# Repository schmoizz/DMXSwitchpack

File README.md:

# DMXSwitchpack
This project includes the PCB and Firmware to build a DIY DMX Switchpack

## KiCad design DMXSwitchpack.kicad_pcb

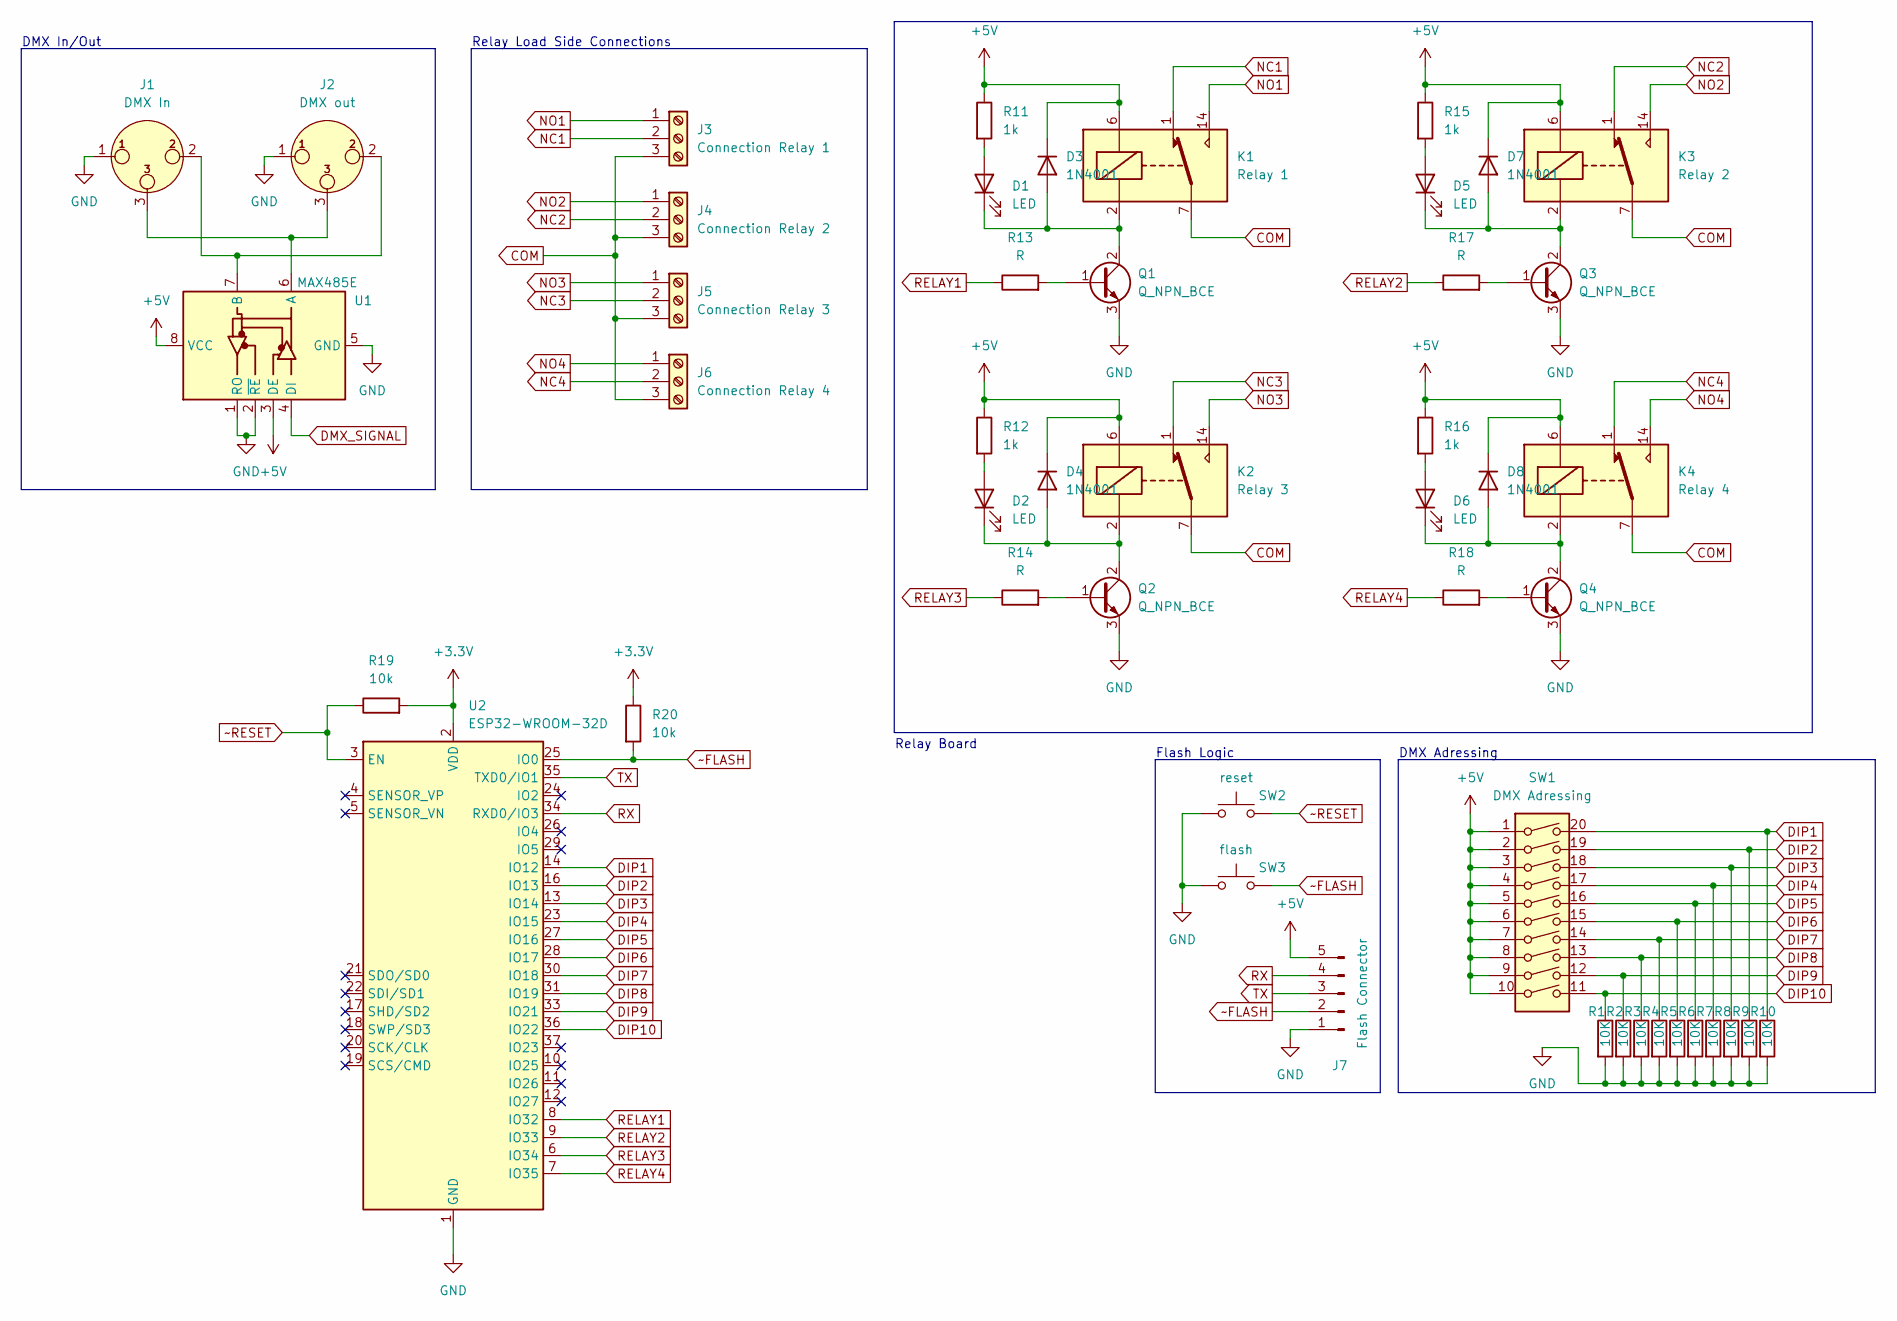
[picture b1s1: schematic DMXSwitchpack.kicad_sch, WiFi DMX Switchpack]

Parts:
D1, D2, D5, D6: LED; LED_0805_2012Metric_Pad1.15x1.40mm_HandSolder
D3, D4, D7, D8: 1N4001; D_DO-41_SOD81_P10.16mm_Horizontal
J1: DMX In; Jack_XLR_Neutrik_NC3FAAH-0_Horizontal
J2: DMX out; Jack_XLR_Neutrik_NC3FAAH-0_Horizontal
J3: Connection Relay 1; TerminalBlock_bornier-3_P5.08mm
J4: Connection Relay 2; TerminalBlock_bornier-3_P5.08mm
J5: Connection Relay 3; TerminalBlock_bornier-3_P5.08mm
J6: Connection Relay 4; TerminalBlock_bornier-3_P5.08mm
J7: Flash Connector; PinHeader_1x05_P2.54mm_Vertical
K1: Relay 1; Relay_StandexMeder_DIP_LowProfile
K2: Relay 3; Relay_StandexMeder_DIP_LowProfile
K3: Relay 2; Relay_StandexMeder_DIP_LowProfile
K4: Relay 4; Relay_StandexMeder_DIP_LowProfile
Q1, Q2, Q3, Q4: Q_NPN_BCE; LaserDiode_TO3.3-D3.3-3
R1, R2, R3, R4, R5, R6, R7, R8, R9, R10: 10K; R_0805_2012Metric_Pad1.20x1.40mm_HandSolder
R11, R12, R15, R16: 1k; R_0805_2012Metric_Pad1.20x1.40mm_HandSolder
R13, R14, R17, R18: R; R_0805_2012Metric_Pad1.20x1.40mm_HandSolder
R19, R20: 10k; R_0805_2012Metric_Pad1.20x1.40mm_HandSolder
SW1: DMX Adressing; SW_DIP_SPSTx10_Slide_9.78x27.58mm_W7.62mm_P2.54mm
SW2: reset; SW_PUSH_6mm_H5mm
SW3: flash; SW_PUSH_6mm_H5mm
U1: MAX485E; Broadcom_LGA-8_2x2mm_P0.53mm
U2: ESP32-WROOM-32D; ESP32-WROOM-32

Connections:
+3.3V: R19.2, R20.1, U2.2 (VDD)
+5V: D3.1 (K), D4.1 (K), D7.1 (K), D8.1 (K), J7.5, K1.6, K2.6, K3.6, K4.6, R11.1, R12.1, R15.1, R16.1, SW1.1, SW1.2, SW1.3, SW1.4, SW1.5, SW1.6, SW1.7, SW1.8, SW1.9, SW1.10, U1.3 (DE), U1.8 (VCC)
COM: J3.3, J4.3, J5.3, J6.3, K1.7, K1.8, K2.7, K2.8, K3.7, K3.8, K4.7, K4.8
DIP1: R10.1, SW1.20, U2.14 (IO12)
DIP2: R9.1, SW1.19, U2.16 (IO13)
DIP3: R8.1, SW1.18, U2.13 (IO14)
DIP4: R7.1, SW1.17, U2.23 (IO15)
DIP5: R6.1, SW1.16, U2.27 (IO16)
DIP6: R5.1, SW1.15, U2.28 (IO17)
DIP7: R4.1, SW1.14, U2.30 (IO18)
DIP8: R3.1, SW1.13, U2.31 (IO19)
DIP9: R2.1, SW1.12, U2.33 (IO21)
DIP10: R1.1, SW1.11, U2.36 (IO22)
DMX_SIGNAL: U1.4 (DI)
GND: J1.1, J2.1, J7.1, Q1.3 (E), Q2.3 (E), Q3.3 (E), Q4.3 (E), R1.2, R2.2, R3.2, R4.2, R5.2, R6.2, R7.2, R8.2, R9.2, R10.2, SW2.1 (A), SW2.2 (A), SW3.1 (A), SW3.2 (A), U1.1 (RO), U1.2 (~RE), U1.5 (GND), U2.1 (GND), U2.15 (GND), U2.38 (GND), U2.39 (GND)
NC1: J3.2, K1.1
NC2: J4.2, K3.1
NC3: J5.2, K2.1
NC4: J6.2, K4.1
NO1: J3.1, K1.14
NO2: J4.1, K3.14
NO3: J5.1, K2.14
NO4: J6.1, K4.14
unnamed: D1.1 (K), D3.2 (A), K1.2, Q1.2 (C)
unnamed: D1.2 (A), R11.2
unnamed: D2.1 (K), D4.2 (A), K2.2, Q2.2 (C)
unnamed: D2.2 (A), R12.2
unnamed: D5.1 (K), D7.2 (A), K3.2, Q3.2 (C)
unnamed: D5.2 (A), R15.2
unnamed: D6.1 (K), D8.2 (A), K4.2, Q4.2 (C)
unnamed: D6.2 (A), R16.2
unnamed: J1.2, J2.2, U1.7 (B)
unnamed: J1.3, J2.3, U1.6 (A)
unnamed: Q1.1 (B), R13.2
unnamed: Q2.1 (B), R14.2
unnamed: Q3.1 (B), R17.2
unnamed: Q4.1 (B), R18.2
RELAY1: R13.1, U2.8 (IO32)
RELAY2: R17.1, U2.9 (IO33)
RELAY3: R14.1, U2.6 (IO34)
RELAY4: R18.1, U2.7 (IO35)
RX: J7.4, U2.34 (RXD0/IO3)
TX: J7.3, U2.35 (TXD0/IO1)
~FLASH: J7.2, R20.2, SW3.3 (B), SW3.4 (B), U2.25 (IO0)
~RESET: R19.1, SW2.3 (B), SW2.4 (B), U2.3 (EN)

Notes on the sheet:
Flash Logic
Relay Board
Relay Load Side Connections
DMX In/Out
DMX Adressing

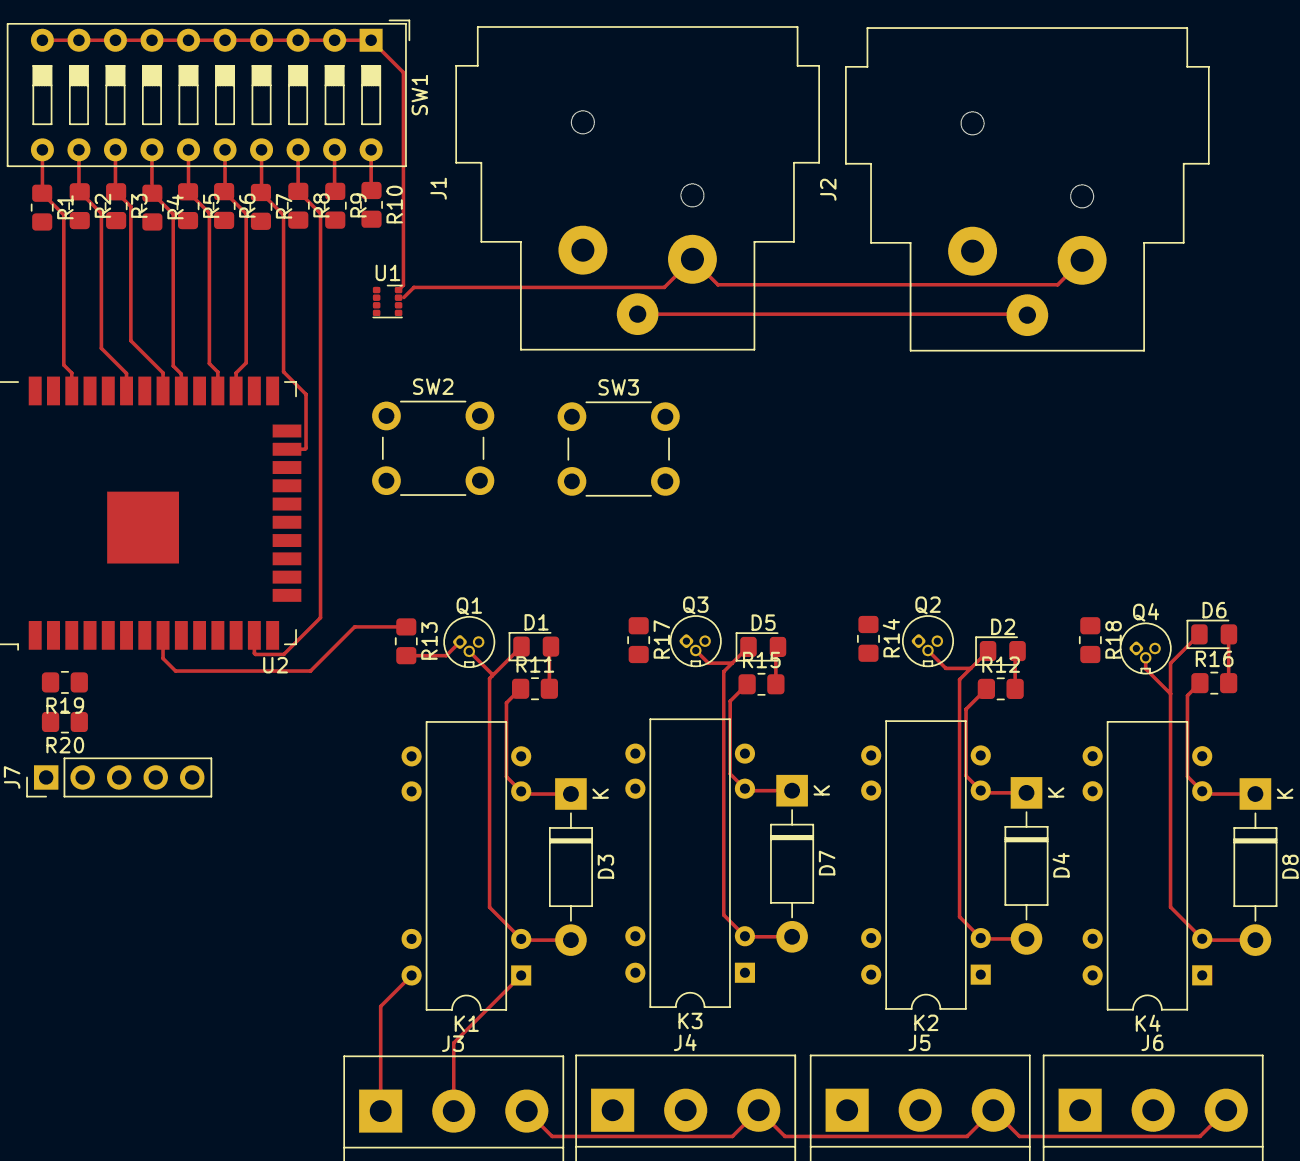
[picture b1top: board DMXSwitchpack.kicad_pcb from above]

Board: 2 copper layers, 48 parts (0 on the bottom side), 44 nets.

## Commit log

2022-09-06 Initial PCB
